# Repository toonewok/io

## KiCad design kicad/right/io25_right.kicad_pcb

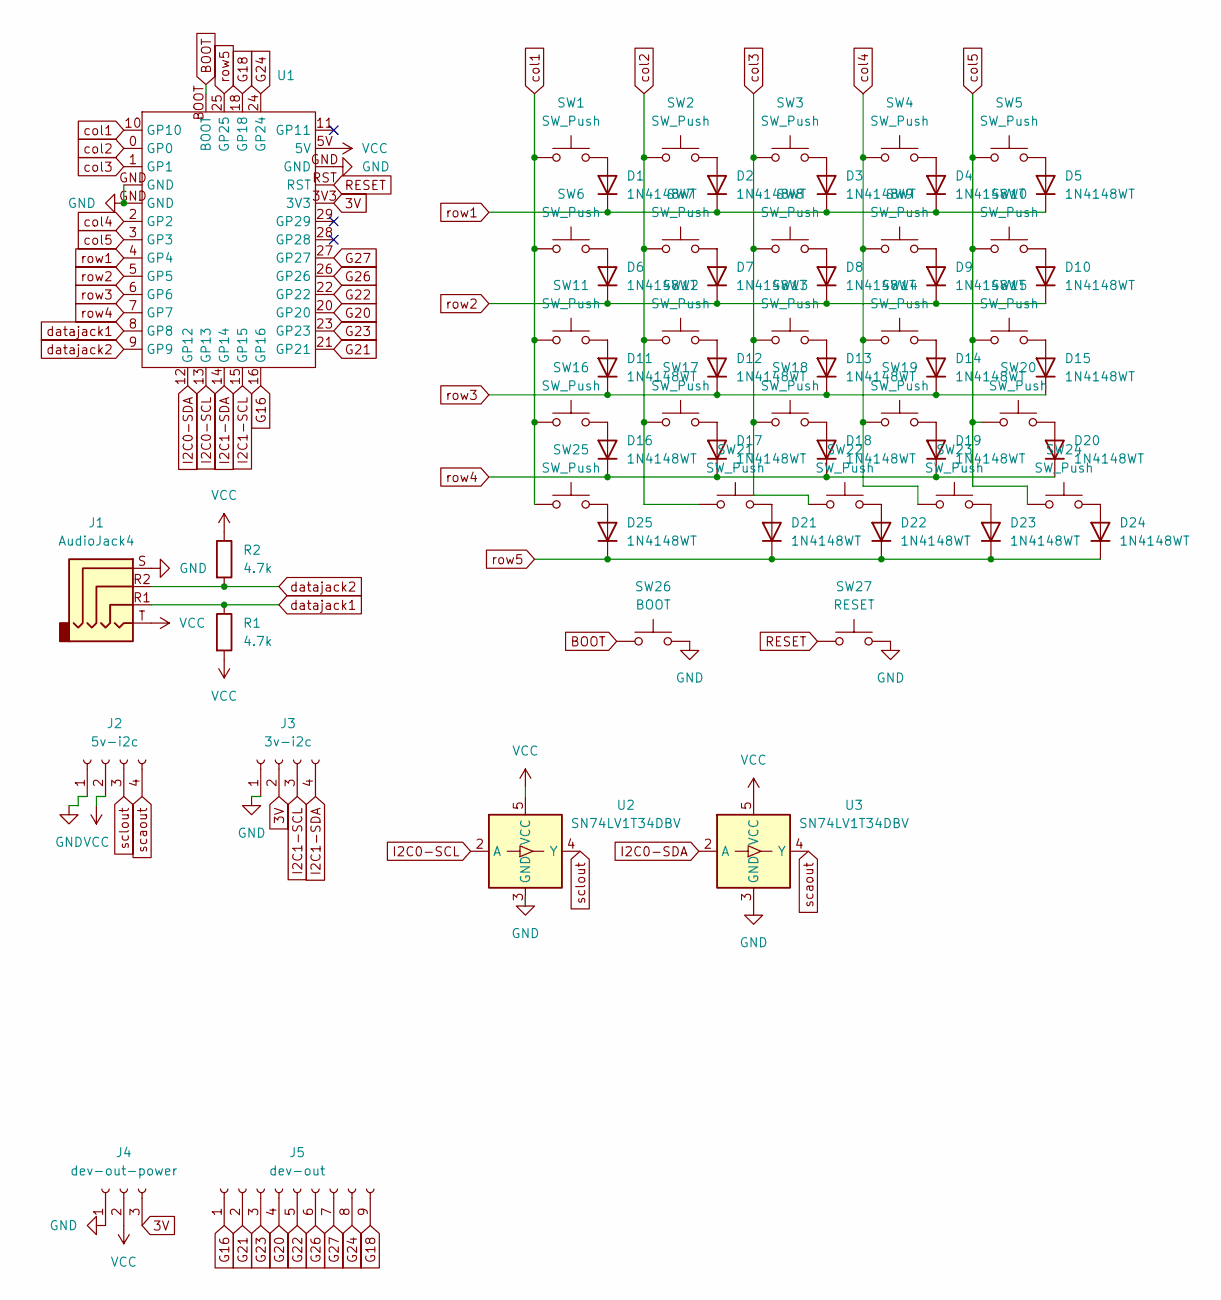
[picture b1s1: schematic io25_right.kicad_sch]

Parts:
D1, D2, D3, D4, D5, D6, D7, D8, D9, D10, D11, D12, D13, D14, D15, D16, D17, D18, D19, D20, D21, D22, D23, D24, D25: 1N4148WT; 1N4148W
J1: AudioJack4; JACK_54-00176_tensility
J2: 5v-i2c; PinHeader_1x04_P2.54mm_Vertical
J3: 3v-i2c; PinHeader_1x04_P2.54mm_Vertical
J4: dev-out-power; PinHeader_1x03_P2.54mm_Vertical
J5: dev-out; PinHeader_2x05_P2.54mm_Vertical
R1, R2: 4.7k; ARG05FTC4701
SW1, SW2, SW3, SW4, SW5, SW6, SW7, SW8, SW9, SW10, SW11, SW12, SW13, SW14, SW15, SW16, SW17, SW18, SW19, SW20, SW21, SW22, SW23, SW24, SW25: SW_Push; mx-choc-dual
SW26: BOOT; SW_PUSH_6mm
SW27: RESET; SW_PUSH_6mm
U1: pro_micro_rp2040
U2, U3: SN74LV1T34DBV; SOT-23-5

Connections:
3V: J3.2, J4.3, U1.3V3
BOOT: SW26.1, U1.BOOT
G16: J5.1, U1.16 (GP16)
G18: J5.9, U1.18 (GP18)
G20: J5.4, U1.20 (GP20)
G21: J5.2, U1.21 (GP21)
G22: J5.5, U1.22 (GP22)
G23: J5.3, U1.23 (GP23)
G24: J5.8, U1.24 (GP24)
G26: J5.6, U1.26 (GP26)
G27: J5.7, U1.27 (GP27)
GND: J1.S, J2.1, J3.1, J4.1, SW26.2, SW27.2, U1.GND, U2.3 (GND), U3.3 (GND)
I2C0-SCL: U1.13 (GP13), U2.2 (A)
I2C0-SDA: U1.12 (GP12), U3.2 (A)
I2C1-SCL: J3.3, U1.15 (GP15)
I2C1-SDA: J3.4, U1.14 (GP14)
unnamed: D1.2 (A), SW1.2
unnamed: D2.2 (A), SW2.2
unnamed: D3.2 (A), SW3.2
unnamed: D4.2 (A), SW4.2
unnamed: D5.2 (A), SW5.2
unnamed: D6.2 (A), SW6.2
unnamed: D7.2 (A), SW7.2
unnamed: D8.2 (A), SW8.2
unnamed: D9.2 (A), SW9.2
unnamed: D10.2 (A), SW10.2
unnamed: D11.2 (A), SW11.2
unnamed: D12.2 (A), SW12.2
unnamed: D13.2 (A), SW13.2
unnamed: D14.2 (A), SW14.2
unnamed: D15.2 (A), SW15.2
unnamed: D16.2 (A), SW16.2
unnamed: D17.2 (A), SW17.2
unnamed: D18.2 (A), SW18.2
unnamed: D19.2 (A), SW19.2
unnamed: D20.2 (A), SW20.2
unnamed: D21.2 (A), SW21.2
unnamed: D22.2 (A), SW22.2
unnamed: D23.2 (A), SW23.2
unnamed: D24.2 (A), SW24.2
unnamed: D25.2 (A), SW25.2
RESET: SW27.1, U1.RST
VCC: J1.T, J2.2, J4.2, R1.2, R2.1, U1.5V, U2.5 (VCC), U3.5 (VCC)
col1: SW1.1, SW6.1, SW11.1, SW16.1, SW25.1, U1.10 (GP10)
col2: SW2.1, SW7.1, SW12.1, SW17.1, SW21.1, U1.0 (GP0)
col3: SW3.1, SW8.1, SW13.1, SW18.1, SW22.1, U1.1 (GP1)
col4: SW4.1, SW9.1, SW14.1, SW19.1, SW23.1, U1.2 (GP2)
col5: SW5.1, SW10.1, SW15.1, SW20.1, SW24.1, U1.3 (GP3)
datajack1: J1.R1, R1.1, U1.8 (GP8)
datajack2: J1.R2, R2.2, U1.9 (GP9)
row1: D1.1 (K), D2.1 (K), D3.1 (K), D4.1 (K), D5.1 (K), U1.4 (GP4)
row2: D6.1 (K), D7.1 (K), D8.1 (K), D9.1 (K), D10.1 (K), U1.5 (GP5)
row3: D11.1 (K), D12.1 (K), D13.1 (K), D14.1 (K), D15.1 (K), U1.6 (GP6)
row4: D16.1 (K), D17.1 (K), D18.1 (K), D19.1 (K), D20.1 (K), U1.7 (GP7)
row5: D21.1 (K), D22.1 (K), D23.1 (K), D24.1 (K), D25.1 (K), U1.25 (GP25)
scaout: J2.4, U3.4 (Y)
sclout: J2.3, U2.4 (Y)

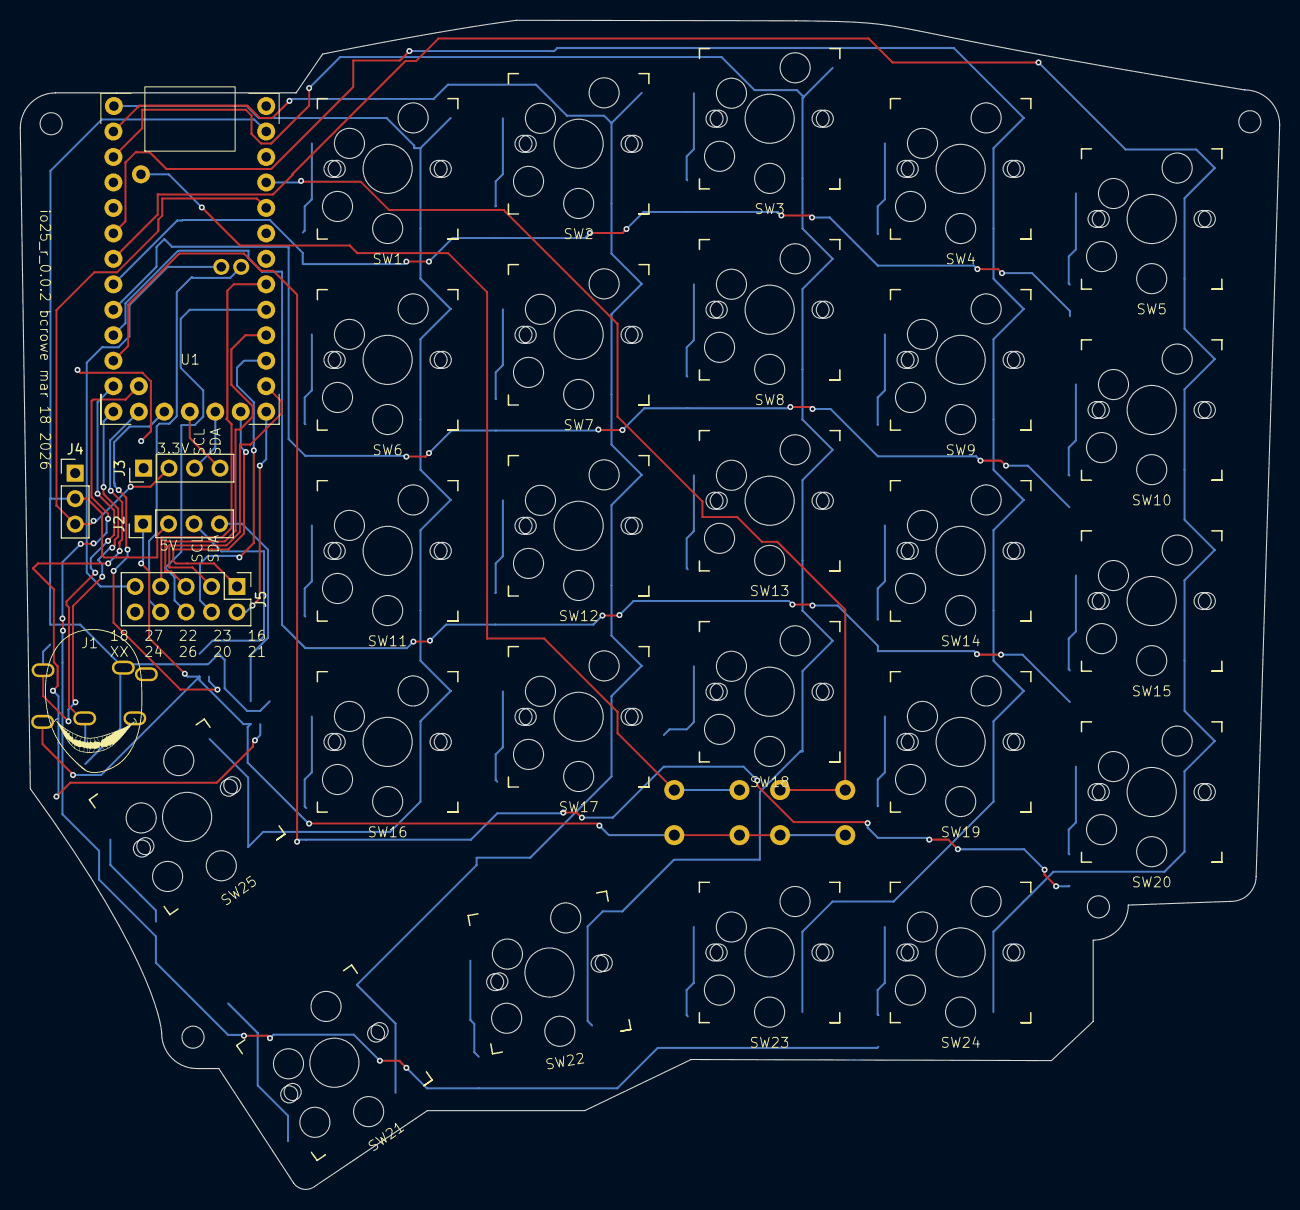
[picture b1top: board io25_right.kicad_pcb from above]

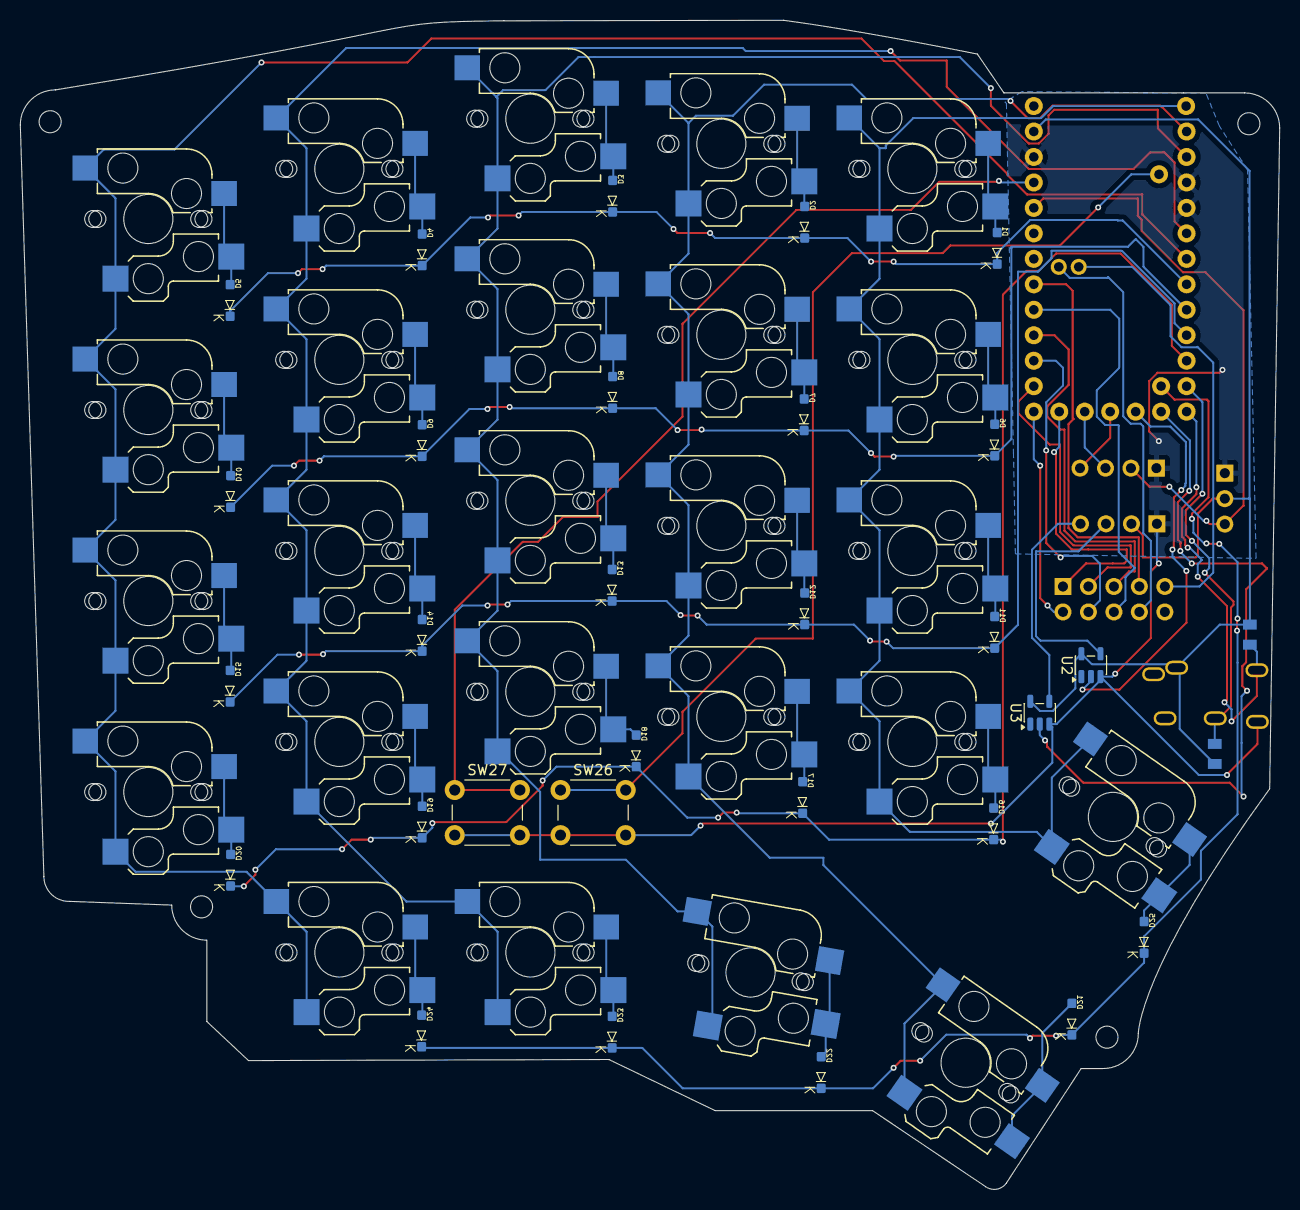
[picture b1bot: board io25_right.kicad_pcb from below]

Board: 2 copper layers, 125.6 x 116.6 mm, 62 parts (6 on the bottom side), 57 nets.

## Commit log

2026-03-25 added base kicad files and code.py
2026-03-27 base layer complete, pins setup
2026-03-27 stop tracking prl lmao
2026-03-28 added left side config, could abort to add rightside but screw it lol
2026-03-28 added right side code config
2026-03-28 removed original code.py from staging
2026-03-28 added layout png
2026-03-30 fixed initial bugs
